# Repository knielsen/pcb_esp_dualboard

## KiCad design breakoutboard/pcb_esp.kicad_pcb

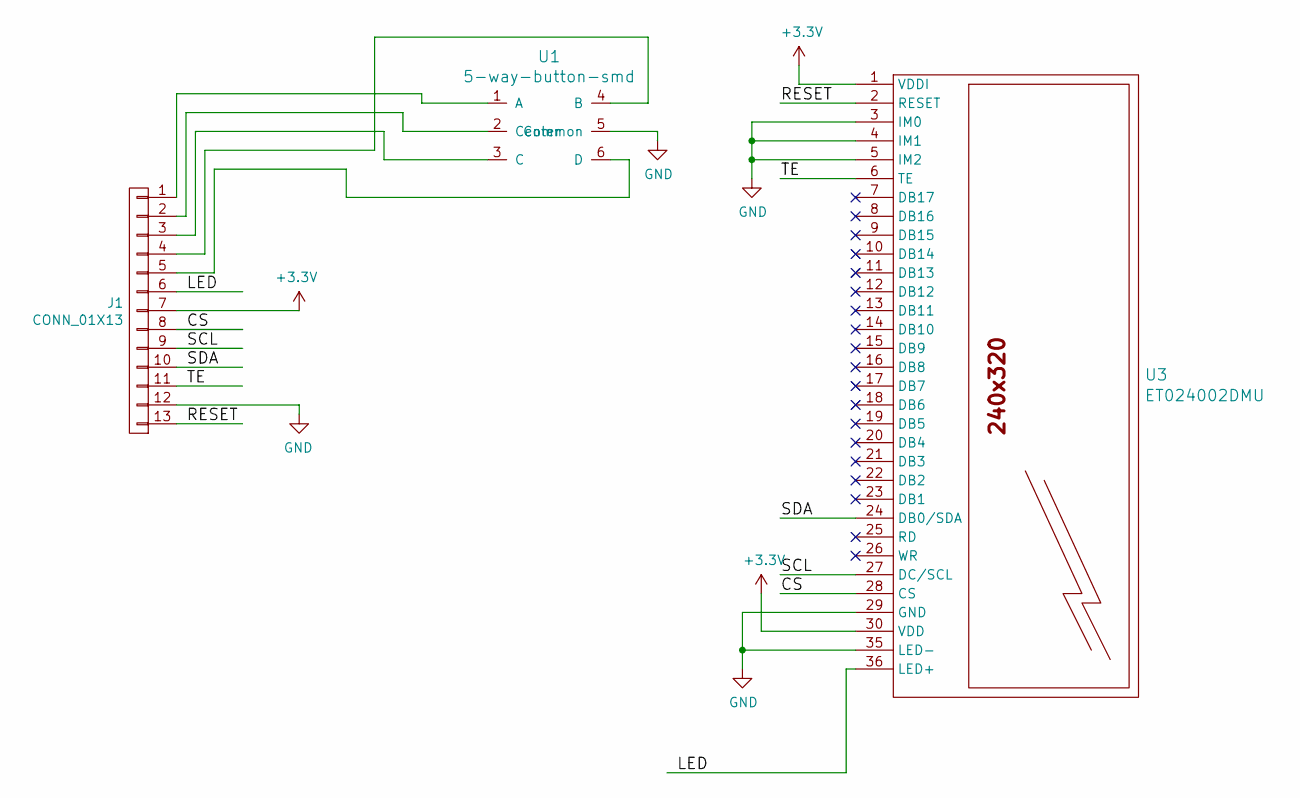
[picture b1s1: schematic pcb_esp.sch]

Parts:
J1: CONN_01X13; Pin_Header_Straight_1x13_Pitch2.54mm
U1: 5-way-button-smd
U3: ET024002DMU

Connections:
+3V3: J1.7, U3.1 (VDDI), U3.30 (VDD)
/CS: J1.8, U3.28 (CS)
/LED: J1.6, U3.36 (LED+)
/RESET: J1.13, U3.2 (RESET)
/SCL: J1.9, U3.27 (DC/SCL)
/SDA: J1.10, U3.24 (DB0/SDA)
/TE: J1.11, U3.6 (TE)
GND: J1.12, U1.5 (Common), U3.3 (IM0), U3.4 (IM1), U3.5 (IM2), U3.29 (GND), U3.35 (LED-)
unnamed: J1.1, U1.1 (A)
unnamed: J1.2, U1.2 (Center)
unnamed: J1.3, U1.3 (C)
unnamed: J1.4, U1.4 (B)
unnamed: J1.5, U1.6 (D)

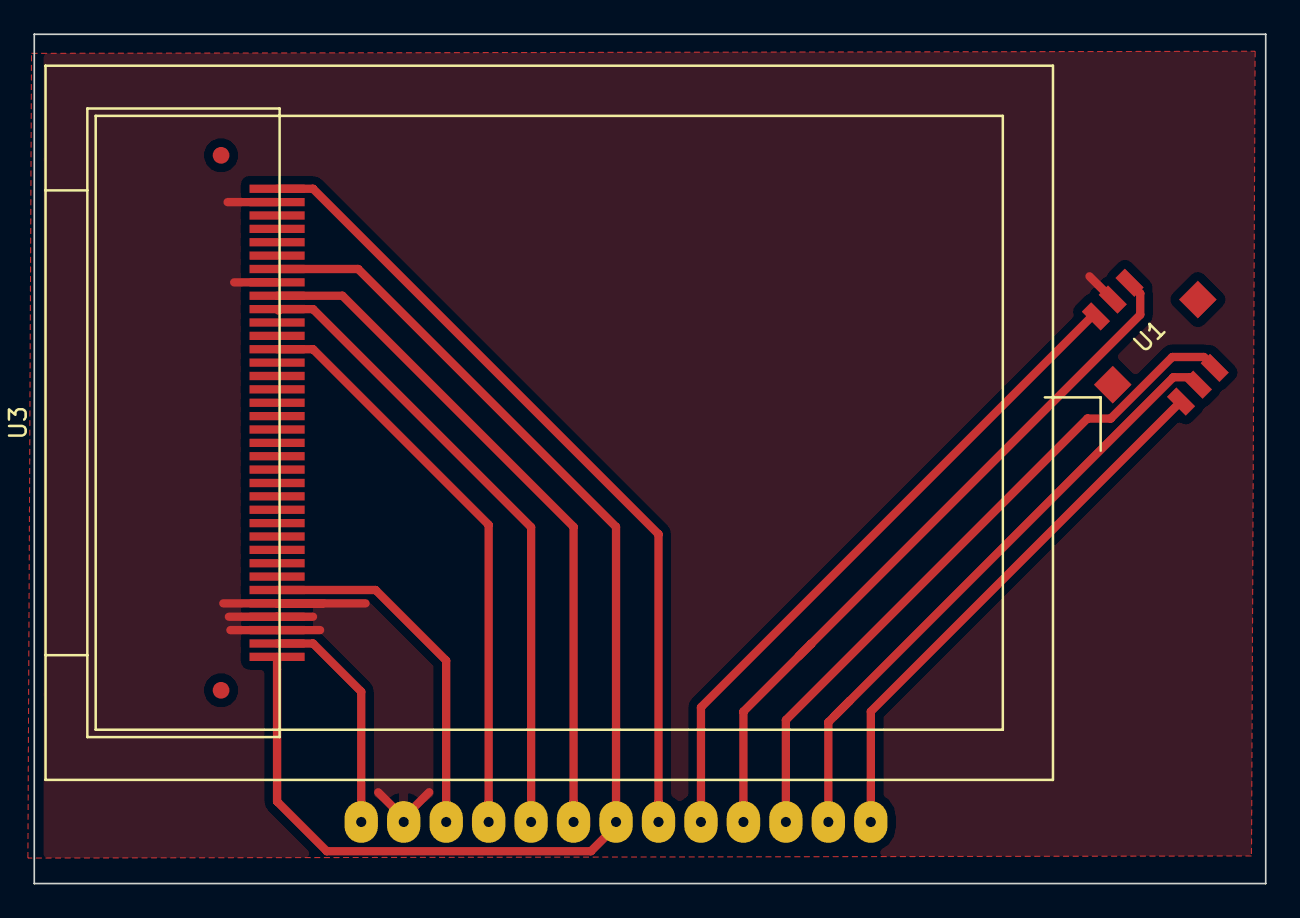
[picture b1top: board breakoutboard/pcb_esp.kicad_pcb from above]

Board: 2 copper layers, 73.7 x 50.8 mm, 3 parts (1 on the bottom side), 13 nets.

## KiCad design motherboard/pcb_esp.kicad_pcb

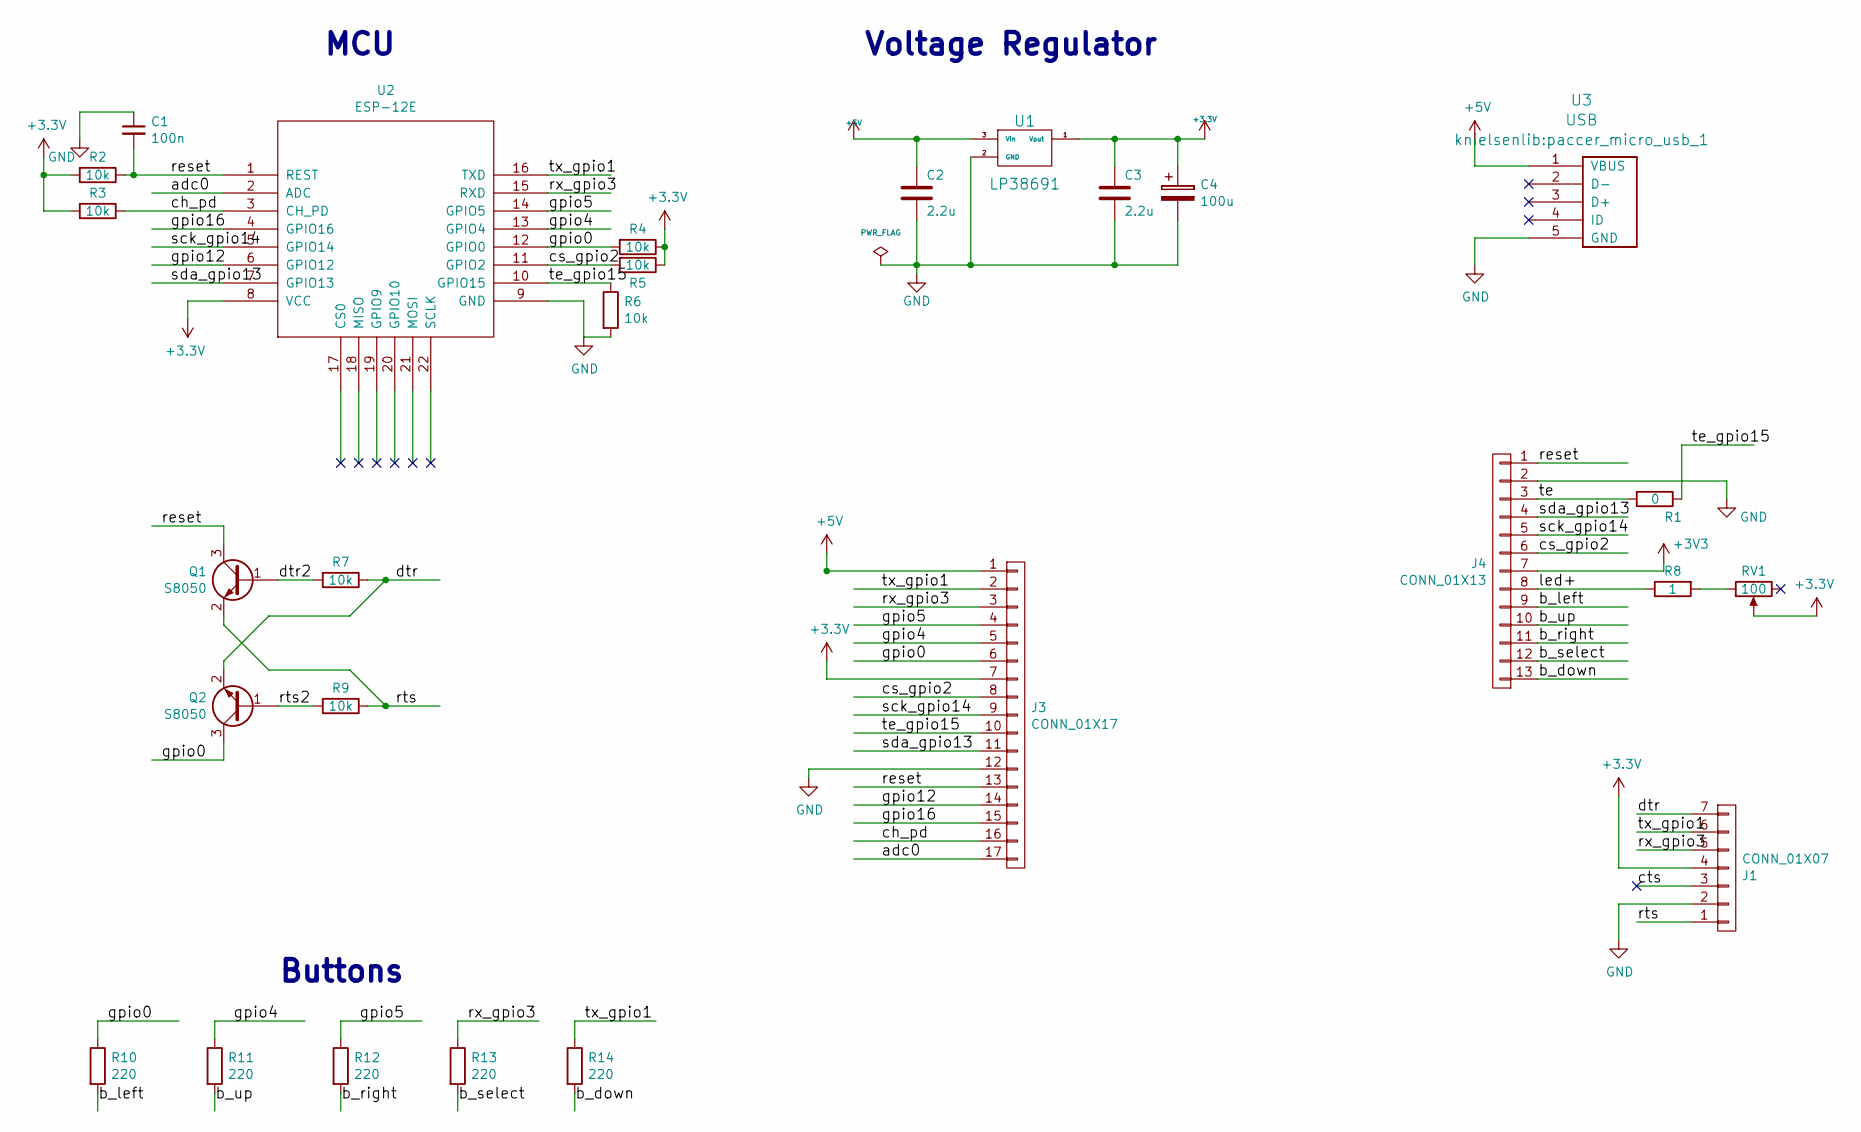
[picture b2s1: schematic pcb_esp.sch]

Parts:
C1: 100n; C_0805_HandSoldering
C2, C3: 2.2u; C_0805_HandSoldering
C4: 100u; CP_Tantalum_Case-U_EIA-6032-15_Hand
J1: CONN_01X07; Pin_Header_Angled_1x07_Pitch2.54mm
J3: CONN_01X17; Pin_Header_Angled_1x17_Pitch2.54mm
J4: CONN_01X13; Socket_Strip_Straight_1x13_Pitch2.54mm
Q1, Q2: S8050; SOT-23_Handsoldering
R1: 0; R_0805_HandSoldering
R2, R3, R4, R5, R6, R7, R9: 10k; R_0805_HandSoldering
R8: 1; R_0603_HandSoldering
R10, R11, R12, R13, R14: 220; R_0805_HandSoldering
RV1: 100; Potentiometer_Trimmer_Bourns_3296W
U1: LP38691; TO-252-3
U2: ESP-12E; ESP-12E_SMD
U3: USB; paccer_micro_usb_1

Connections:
+5V: C2.1, J3.1, U1.3 (Vin), U3.1 (VBUS)
/adc0: J3.17, U2.2 (ADC)
/b_down: J4.13, R14.2
/b_left: J4.9, R10.2
/b_right: J4.11, R12.2
/b_select: J4.12, R13.2
/b_up: J4.10, R11.2
/ch_pd: J3.16, R3.1, U2.3 (CH_PD)
/cs_gpio2: J3.8, J4.6, R5.2, U2.11 (GPIO2)
/cts: J1.3
/dtr: J1.7, Q2.2 (E), R7.1
/dtr2: Q1.1 (B), R7.2
/gpio0: J3.6, Q2.3 (C), R4.2, R10.1, U2.12 (GPIO0)
/gpio4: J3.5, R11.1, U2.13 (GPIO4)
/gpio5: J3.4, R12.1, U2.14 (GPIO5)
/gpio12: J3.14, U2.6 (GPIO12)
/gpio16: J3.15, U2.4 (GPIO16)
/led+: J4.8, R8.1
/reset: C1.2, J3.13, J4.1, Q1.3 (C), R2.1, U2.1 (REST)
/rts: J1.1, Q1.2 (E), R9.1
/rts2: Q2.1 (B), R9.2
/rx_gpio3: J1.5, J3.3, R13.1, U2.15 (RXD)
/sck_gpio14: J3.9, J4.5, U2.5 (GPIO14)
/sda_gpio13: J3.11, J4.4, U2.7 (GPIO13)
/te: J4.3, R1.2
/te_gpio15: J3.10, R1.1, R6.1, U2.10 (GPIO15)
/tx_gpio1: J1.6, J3.2, R14.1, U2.16 (TXD)
GND: C1.1, C2.2, C3.2, C4.2, J1.2, J3.12, J4.2, R6.2, U1.2 (GND), U2.9 (GND), U3.5 (GND)
unnamed: R8.2, RV1.1

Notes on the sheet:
Voltage Regulator
MCU
Buttons

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
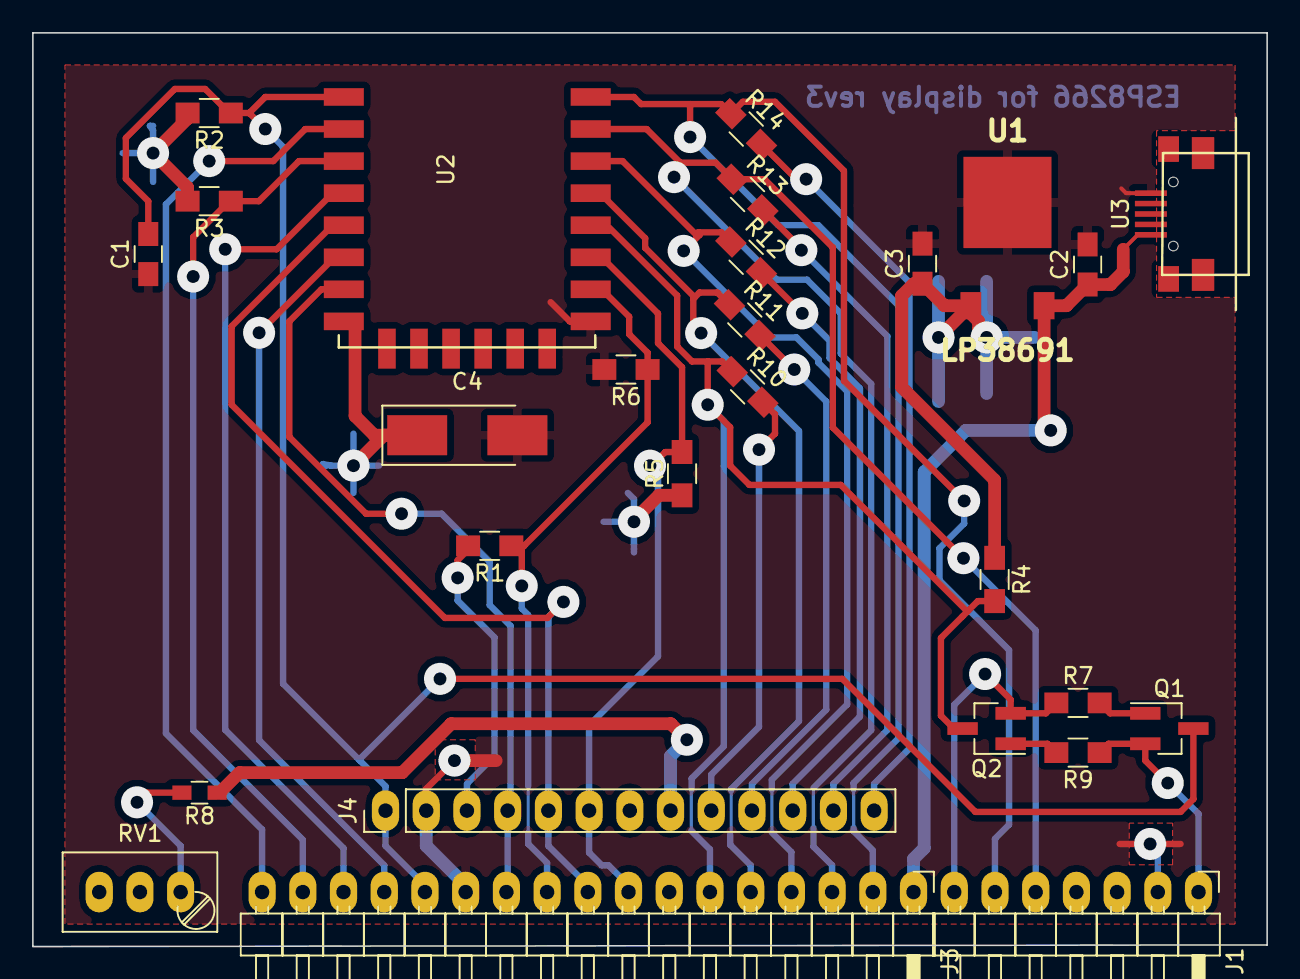
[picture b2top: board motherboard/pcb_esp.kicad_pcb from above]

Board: 2 copper layers, 77.0 x 57.0 mm, 27 parts (0 on the bottom side), 29 nets.

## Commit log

2017-07-24 Initial revision
2017-07-24 Move to subdir, in preparation for including breakout board.
2017-07-25 Small fixes
2017-07-29 First revision of new, double-sided ESP motherboard for display
2017-07-29 Small fixes in routing.
2017-08-05 Version rev2 for double-sided etching.
2017-08-05 Post-rev2 fixes for clearances and zones
2017-08-05 Few routing tweaks following increased clearances
2017-08-12 Breakout board
    Breakout board for the ST7787 based display
